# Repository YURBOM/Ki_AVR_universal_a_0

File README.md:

# Universal KiCAD PCB template for ATMEGA 644/1284

## Key features of the project

### Versatile
Two types of packages (DIP-40 and TQFP-44) on one board.

### Reset control
Keep one microcontroller in reset state to use the other.

### Easy upgradeability
Unique hardware upgradeability of your device thanks to the DIP package

### Open Source
The project is distributed under the MIT license

### Optimized design
Designed for dual-layer PCBs with adaptability

## Our solution is particularly useful for:

- Developers working with prototypes
- Educational projects
- Small batch production
- Experimental development

### Technical realization

The board is designed to maximize port compatibility between both types of packages. Switching between microcontrollers is done via RESET line control, which ensures reliable operation of the system.

### Availability

All project materials, including schematics and PCB files, are available on GitHub.
We welcome community participation in the development of the project and look forward to your suggestions for improvement.

https://yurbom.com/

Contact info@yurbom.com

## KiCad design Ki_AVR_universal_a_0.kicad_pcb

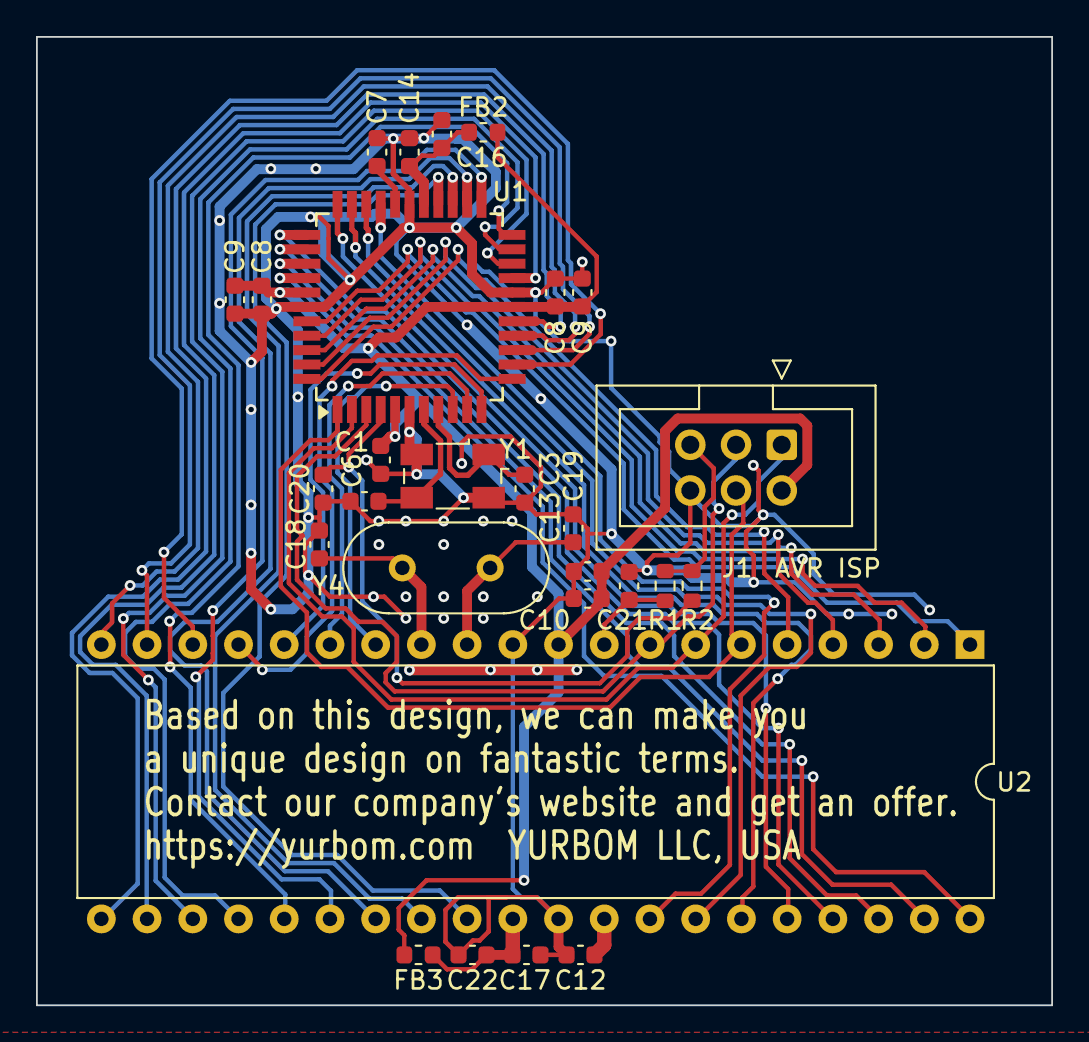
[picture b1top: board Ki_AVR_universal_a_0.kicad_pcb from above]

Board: 2 copper layers, 56.4 x 53.8 mm, 28 parts (0 on the bottom side), 45 nets.

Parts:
C1, C7, C8, C8#2, C10, C12, C14, C17, C20, C21: 100nF; C_0603_1608Metric
C3, C6, C18, C19: 20pF; C_0603_1608Metric
C9, C9#2, C13, C16, C22: 4.7uF; C_0603_1608Metric
FB2, FB3: FB100; L_0603_1608Metric
J1: AVR-ISP-6; IDC-Header_2x03_P2.54mm_Vertical
R1, R2: 0; R_0603_1608Metric
U1: ATmega644P-20A; TQFP-44_10x10mm_P0.8mm
U2: ATmega644-20P; DIP-40_W15.24mm
Y1: 20MHz; Crystal_SMD_Abracon_ABM3B-4Pin_5.0x3.2mm
Y4: 20MHz; Crystal_HC49-4H_Vertical

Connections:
/avr_mcu/MCU_AREF1: C7.1, U1.29 (AREF)
/avr_mcu/MCU_AREF2: C12.1, U2.32 (AREF)
/avr_mcu/MCU_AVCC1: C14.1, C16.1, FB2.2, U1.27 (AVCC)
/avr_mcu/MCU_AVCC2: C17.1, C22.1, FB3.2, U2.30 (AVCC)
/avr_mcu/MCU_PA0: U1.37 (PA0), U2.40 (PA0)
/avr_mcu/MCU_PA1: U1.36 (PA1), U2.39 (PA1)
/avr_mcu/MCU_PA2: U1.35 (PA2), U2.38 (PA2)
/avr_mcu/MCU_PA3: U1.34 (PA3), U2.37 (PA3)
/avr_mcu/MCU_PA4: U1.33 (PA4), U2.36 (PA4)
/avr_mcu/MCU_PA5: U1.32 (PA5), U2.35 (PA5)
/avr_mcu/MCU_PA6: U1.31 (PA6), U2.34 (PA6)
/avr_mcu/MCU_PA7: U1.30 (PA7), U2.33 (PA7)
/avr_mcu/MCU_PB0: U1.40 (PB0), U2.1 (PB0)
/avr_mcu/MCU_PB1: U1.41 (PB1), U2.2 (PB1)
/avr_mcu/MCU_PB2: U1.42 (PB2), U2.3 (PB2)
/avr_mcu/MCU_PB3: U1.43 (PB3), U2.4 (PB3)
/avr_mcu/MCU_PB4: U1.44 (PB4), U2.5 (PB4)
/avr_mcu/MCU_PB5: J1.4 (MOSI), U1.1 (PB5), U2.6 (PB5)
/avr_mcu/MCU_PB6: J1.1 (MISO), U1.2 (PB6), U2.7 (PB6)
/avr_mcu/MCU_PB7: J1.3 (SCK), U1.3 (PB7), U2.8 (PB7)
/avr_mcu/MCU_PD0: U1.9 (PD0), U2.14 (PD0)
/avr_mcu/MCU_PD1: U1.10 (PD1), U2.15 (PD1)
/avr_mcu/MCU_PD2: U1.11 (PD2), U2.16 (PD2)
/avr_mcu/MCU_PD3: U1.12 (PD3), U2.17 (PD3)
/avr_mcu/MCU_PD4: U1.13 (PD4), U2.18 (PD4)
/avr_mcu/MCU_PD5: U1.14 (PD5), U2.19 (PD5)
/avr_mcu/MCU_PD6: U1.15 (PD6), U2.20 (PD6)
/avr_mcu/MCU_PD7: U1.16 (PD7), U2.21 (PD7)
/avr_mcu/MCU_PС0: U1.19 (PC0), U2.22 (PC0)
/avr_mcu/MCU_PС1: U1.20 (PC1), U2.23 (PC1)
/avr_mcu/MCU_PС2: U1.21 (PC2), U2.24 (PC2)
/avr_mcu/MCU_PС3: U1.22 (PC3), U2.25 (PC3)
/avr_mcu/MCU_PС4: U1.23 (PC4), U2.26 (PC4)
/avr_mcu/MCU_PС5: U1.24 (PC5), U2.27 (PC5)
/avr_mcu/MCU_PС6: U1.25 (PC6), U2.28 (PC6)
/avr_mcu/MCU_PС7: U1.26 (PC7), U2.29 (PC7)
/avr_mcu/MCU_nRESET: J1.5 (~RST), R1.2, R2.2
/avr_mcu/MCU_nRESET1: C20.1, R2.1, U1.4 (~RESET)
/avr_mcu/MCU_nRESET2: C21.1, R1.1, U2.9 (~RESET)
GND: C1.2, C3.1, C6.1, C7.2, C8.2, C8#2.2, C9.2, C9#2.2, C10.2, C12.2, C13.2, C14.2, C16.2, C17.2, C18.1, C19.1, C20.2, C21.2, C22.2, J1.6 (GND), U1.6 (GND), U1.18 (GND), U1.28 (GND), U1.39 (GND), U2.11 (GND), U2.31 (GND), Y1.2, Y1.4
unnamed: C3.2, U1.8 (XTAL1), Y1.1
unnamed: C6.2, U1.7 (XTAL2), Y1.3
unnamed: C18.2, U2.13 (XTAL1), Y4.1
unnamed: C19.2, U2.12 (XTAL2), Y4.2
VCC_5V: C1.1, C8.1, C8#2.1, C9.1, C9#2.1, C10.1, C13.1, FB2.1, FB3.1, J1.2 (VCC), U1.5 (VCC), U1.17 (VCC), U1.38 (VCC), U2.10 (VCC)

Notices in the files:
Ki_AVR_universal_a_0.kicad_pcb:
MIT Open Source License - NO ANY WARRANTY. Designed in California, USA.
Copyright 2025, YURBOM LLC
